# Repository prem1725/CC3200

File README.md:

# CC3200

CC3200 SimpleLink Wi-Fi—Consists of
Applications Microcontroller, Wi-Fi Network
Processor, and Power-Management Subsystems

Wi-Fi CERTIFIED™ Chip

Applications Microcontroller Subsystem
  ARM® Cortex®-M4 Core at 80 MHz
  Embedded Memory
    RAM (Up to 256KB)
    External Serial Flash Bootloader, and Peripheral Drivers in ROM
    
  32-Channel Direct Memory Access (µDMA)

  Hardware Crypto Engine for Advanced Fast Security, Including
    AES, DES, and 3DES
    SHA2 and MD5
    CRC and Checksum

  8-Bit Parallel Camera Interface

  1 Multichannel Audio Serial Port (McASP)
  Interface with Support for Two I2S Channels

  1 SD/MMC Interface

  2 Universal Asynchronous Receivers and
  Transmitters (UARTs)

  1 Serial Peripheral Interface (SPI)

  1 Inter-Integrated Circuit (I2C)

  4 General-Purpose Timers with 16-Bit Pulse-
  Width Modulation (PWM) Mode

  1 Watchdog Timer

  4-Channel 12-Bit Analog-to-Digital Converters
  (ADCs)

  Up to 27 Individually Programmable, Multiplexed
  GPIO Pins

Dedicated External SPI Interface for Serial Flash

Wi-Fi Network Processor Subsystem
  Featuring Wi-Fi Internet-On-a-Chip™
  
  Dedicated ARM MCU
  Completely Offloads Wi-Fi and Internet
  Protocols from the Application Microcontroller
  
  Wi-Fi and Internet Protocols in ROM
  
  802.11 b/g/n Radio, Baseband, Medium Access
  Control (MAC), Wi-Fi Driver, and Supplicant
  
  TCP/IP Stack
    Industry-Standard BSD Socket Application
    Programming Interfaces (APIs)
    
    8 Simultaneous TCP or UDP Sockets
    
    2 Simultaneous TLS and SSL Sockets
  Powerful Crypto Engine for Fast, Secure Wi-Fi
  and Internet Connections with 256-Bit AES
  Encryption for TLS and SSL Connections

  Station, AP, and Wi-Fi Direct™ Modes

  WPA2 Personal and Enterprise Security

  SimpleLink Connection Manager for
  Autonomous and Fast Wi-Fi Connections

  SmartConfig™ Technology, AP Mode, and
  WPS2 for Easy and Flexible Wi-Fi Provisioning

  TX Power
    18.0 dBm @ 1 DSSS
    14.5 dBm @ 54 OFDM

  RX Sensitivity
    –95.7 dBm @ 1 DSSS
    –74.0 dBm @ 54 OFDM

  Application Throughput
    UDP: 16 Mbps
    TCP: 13 Mbps

Power-Management Subsystem
  Integrated DC-DC Supports a Wide Range of
  Supply Voltage:
    VBAT Wide-Voltage Mode: 2.1 to 3.6 V
    
    VIO is Always Tied with VBAT
    
    Preregulated 1.85-V Mode

  Advanced Low-Power Modes
    Hibernate: 4 µA
    
    Low-Power Deep Sleep (LPDS): 250 µA
    
    RX Traffic (MCU Active): 59 mA @ 54 OFDM
    
    TX Traffic (MCU Active): 229 mA @ 54 OFDM,
    Maximum Power

    Idle Connected (MCU in LPDS):
    825 µA @ DTIM = 1

Clock Source
  40.0-MHz Crystal with Internal Oscillator
  
  32.768-kHz Crystal or External RTC Clock

Package and Operating Temperature
  0.5-mm Pitch, 64-Pin, 9-mm × 9-mm QFN
  
  Ambient Temperature Range: –40°C to 85°C

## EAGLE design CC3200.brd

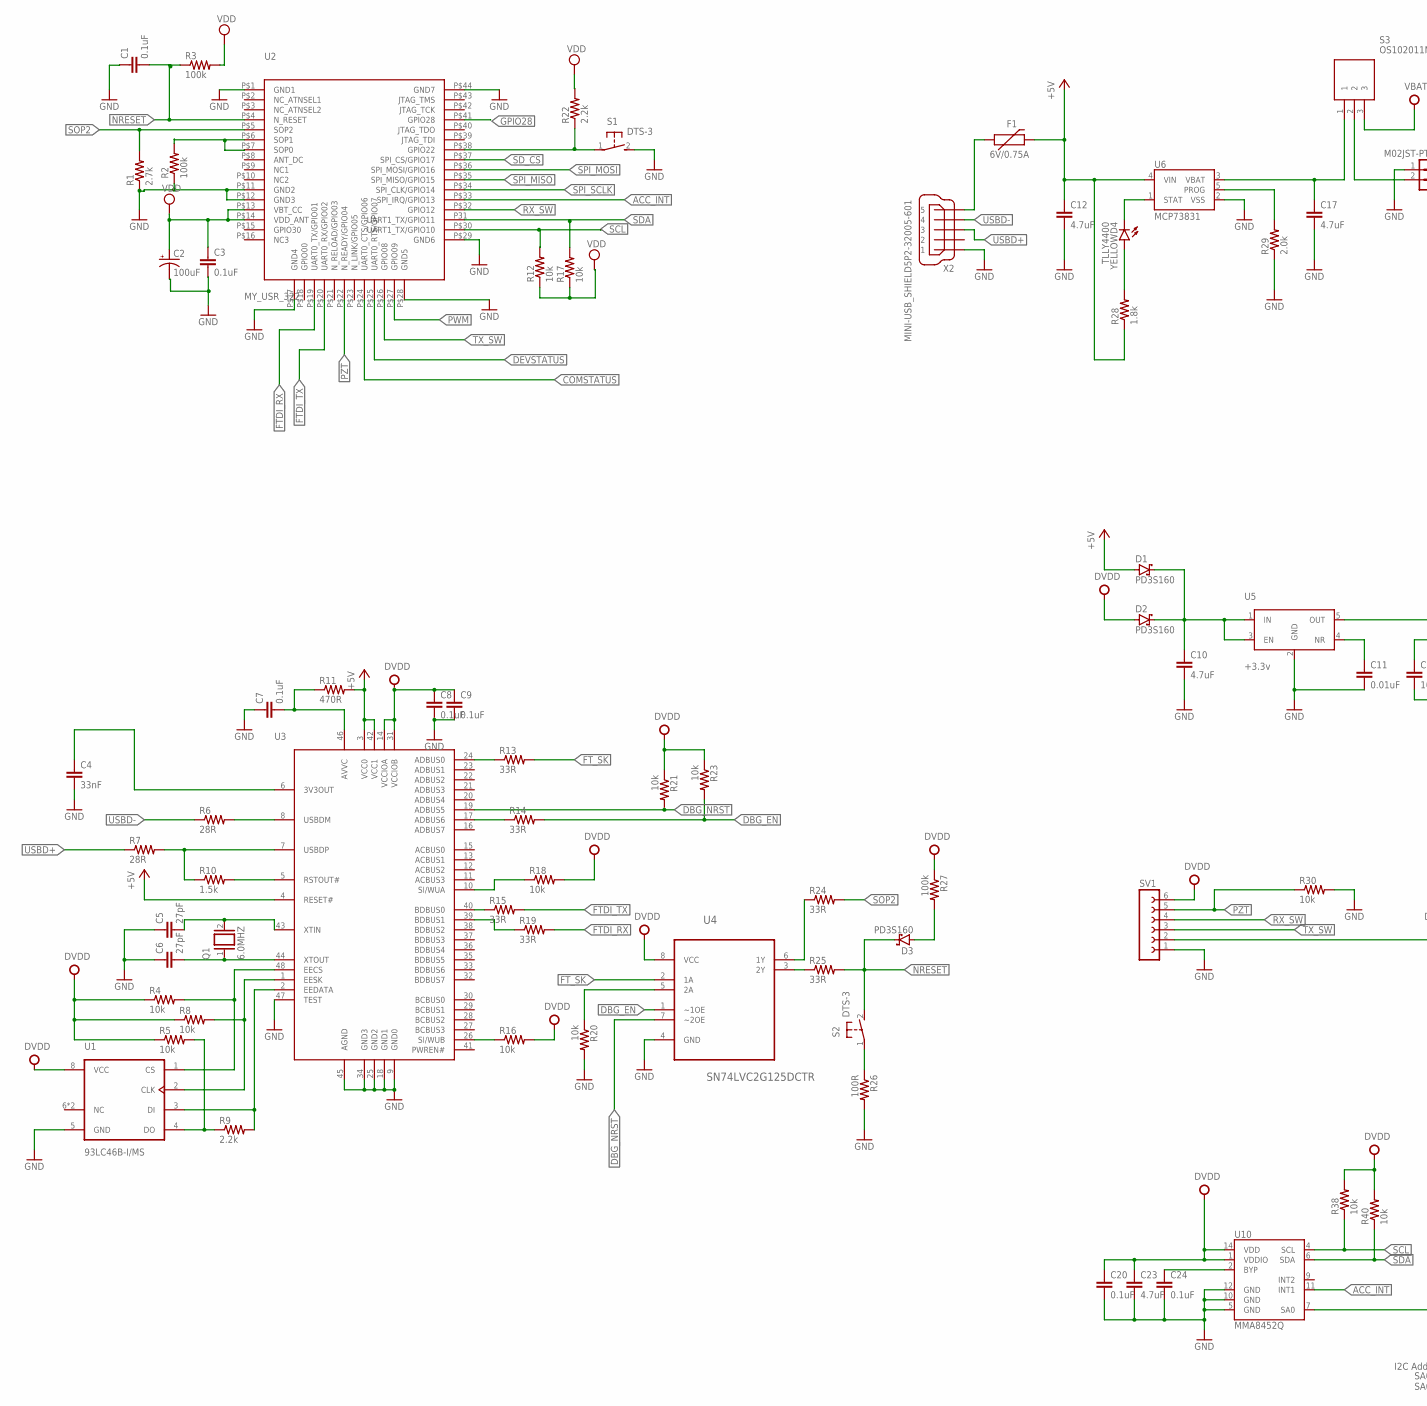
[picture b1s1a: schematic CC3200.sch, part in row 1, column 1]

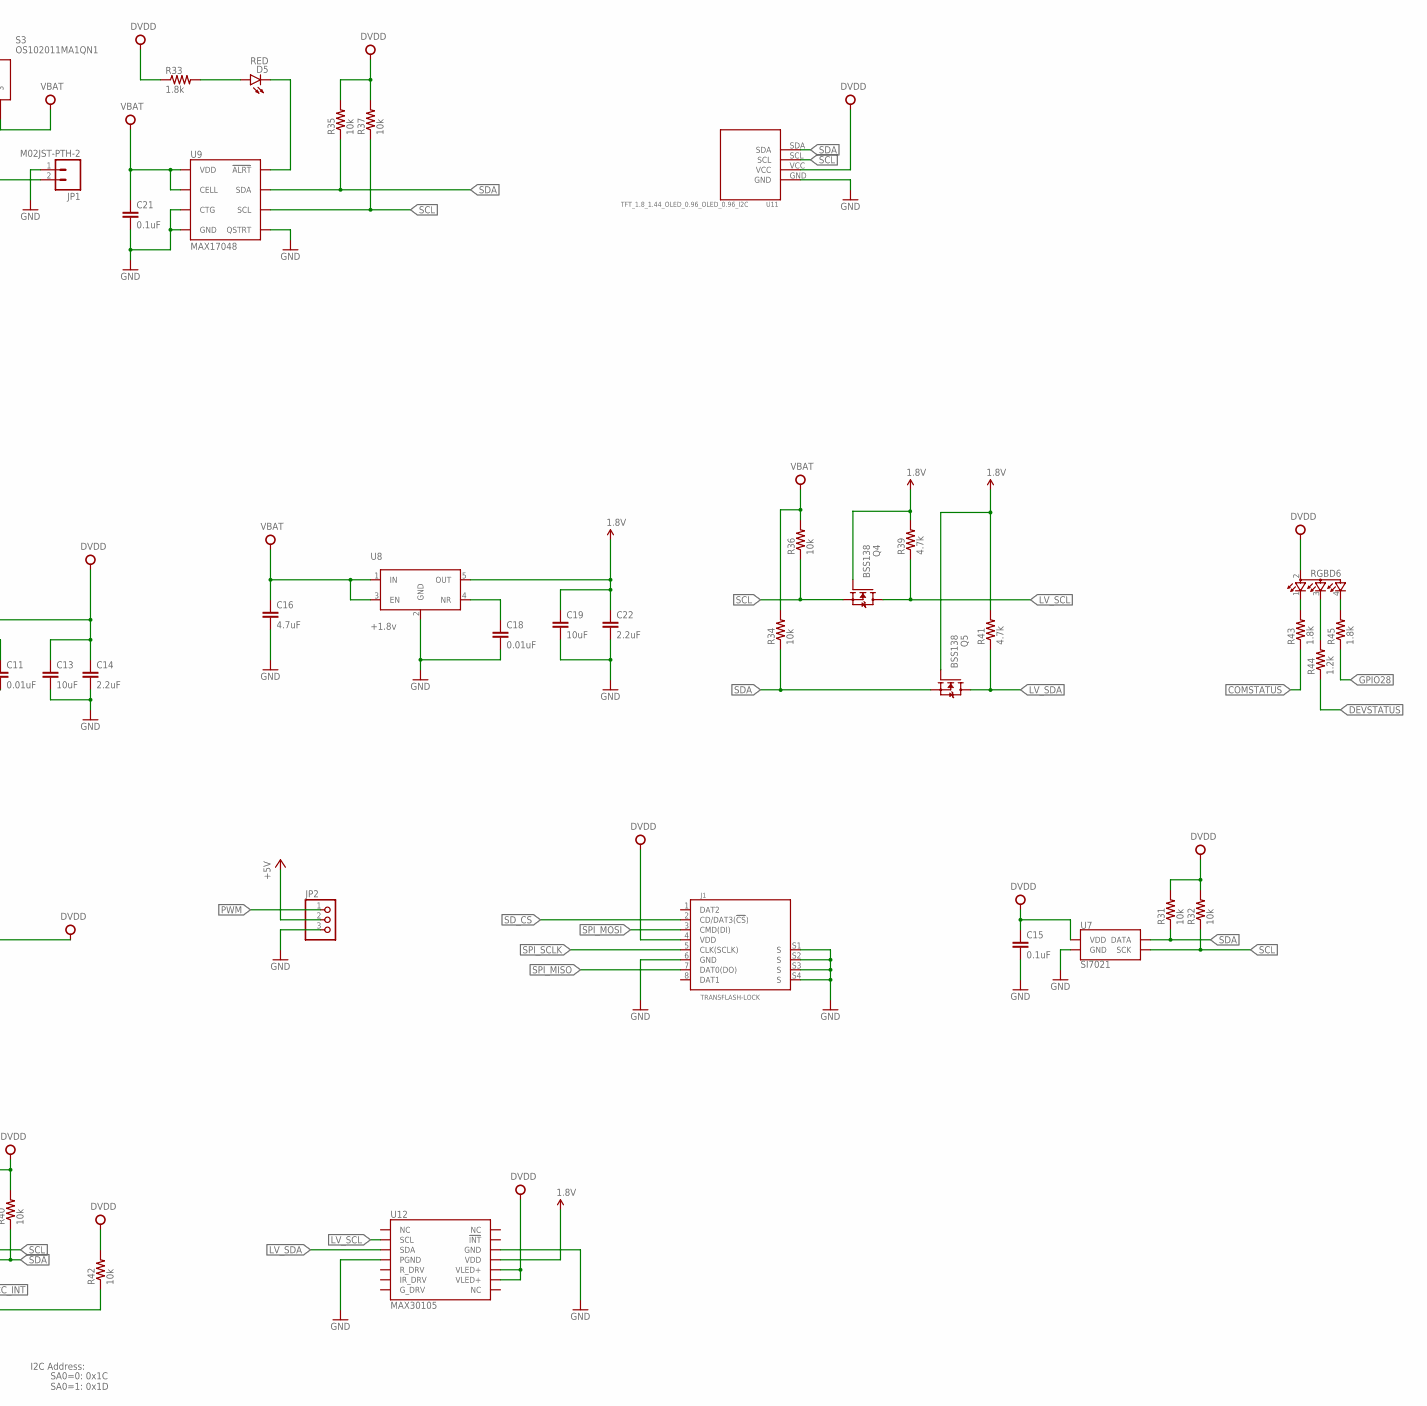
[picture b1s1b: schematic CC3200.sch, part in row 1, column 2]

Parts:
C1, C3: 0.1uF; 0402-TIGHT
C2: 100uF; 1206-POLAR
C4: 33nF; 0603-CAP
C5, C6: 27pF; 0603-CAP
C7, C8, C9, C15, C20, C21, C24: 0.1uF; 0603-CAP
C10, C12, C16, C17, C23: 4.7uF; 0603-CAP
C11, C18: 0.01uF; 0603-CAP
C13, C19: 10uF; 0603-CAP
C14, C22: 2.2uF; 0603-CAP
D1, D2, D3: PD3S160; POWERDI323
D5: RED; LED-0603
F1: 6V/0.75A; 1206
J1: TRANSFLASH-LOCK; TRANSFLASH-LOCK-SOCK
JP1: M02JST-PTH-2; JST-2-PTH
JP2: PINHD-1X3; 1X03
Q1: 6.0MHZ; Q
Q4, Q5: BSS138; SOT23
R1: 2.7k; 0603-RES
R2, R3, R27: 100k; 0603-RES
R4, R5, R8, R12, R16, R17, R18, R20, R21, R23, R30, R31, R32, R34, R35, R36, R37, R38, R40, R42: 10k; 0603-RES
R6, R7: 28R; 0603-RES
R9, R22: 2.2k; 0603-RES
R10: 1.5k; 0603-RES
R11: 470R; 0603-RES
R13, R14, R15, R19, R24, R25: 33R; 0603-RES
R26: 100R; 0603-RES
R28, R33, R43, R45: 1.8k; 0603-RES
R29: 2.0k; 0603-RES
R39, R41: 4.7k; 0603-RES
R44: 1.2k; 0603-RES
RGBD6: TOPLED-3; P-LCC-4-3
S1, S2: DTS-3
S3: OS102011MA1QN1
SV1: FE06-1; FE06
U1: 93LC46B-I/MS; SOP65P490X110-8N
U2: MY_USR_322
U3: FT2232D; LQFP48
U4: SN74LVC2G125DCTR; SOP65P400X130-8N
U5: +3.3v; SOT23-5
U6: MCP73831; SOT23-5
U7: SI7021; DFN-6-3X3-SI7021
U8: +1.8v; SOT23-5
U9: MAX17048; DFN-8
U10: MMA8452Q; QFN-16_0.5MM
U11: TFT_1.8_1.44_OLED_0.96_OLED_0.96_I2C
U12: MAX30105; OLGA-14
X2: MINI-USB_SHIELD5P2-32005-601; 32005-601
YELLOWD4: TLLY4400; LED3MM

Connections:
1.8V: C19.1, C22.1, Q5.1 (G), R39.2, R41.2, U8.5 (OUT), U12.11 (VDD)
+5V: C12.1, D1.A, F1.2, JP2.2, R11.2, R28.1, U3.3 (VCC0), U3.4 (RESET#), U3.42 (VCC1), U6.4 (VIN)
ACC_INT: U2.P$33 (SPI_IRQ/GPIO13), U10.11 (INT1)
COMSTATUS: R43.1, U2.P$24 (UART0_CTS/GPIO06)
DBG_EN: R14.2, R23.2, U4.1 (~1OE)
DBG_NRST: R21.2, U3.19 (ADBUS5), U4.7 (~2OE)
DEVSTATUS: R44.1, U2.P$25 (UART0_RTS/GPIO07)
DVDD: C8.1, C9.1, C13.1, C14.1, C15.1, C20.1, C23.1, D2.A, J1.4 (VDD), R4.1, R5.1, R8.1, R16.2, R18.2, R21.1, R23.1, R27.1, R31.2, R32.2, R33.1, R35.2, R37.2, R38.2, R40.2, R42.2, RGBD6.2 (A2), SV1.2, SV1.6, U1.8 (VCC), U3.14 (VCCIOA), U3.31 (VCCIOB), U4.8 (VCC), U5.5 (OUT), U7.VDD, U10.1 (VDDIO), U10.14 (VDD), U11.VCC, U12.9 (VLED+), U12.10 (VLED+)
FTDI_RX: R19.2, U2.P$19 (UART0_TX/GPIO01)
FTDI_TX: R15.2, U2.P$20 (UART0_RX/GPIO02)
FT_SK: R13.2, U4.2 (1A)
GND: C1.1, C3.2, C4.2, C5.1, C6.1, C7.1, C8.2, C9.2, C10.2, C11.2, C12.2, C13.2, C14.2, C15.2, C16.2, C17.2, C18.2, C19.2, C20.2, C21.2, C22.2, C23.2, C24.2, J1.6 (GND), J1.S1 (S), J1.S2 (S), J1.S3 (S), J1.S4 (S), JP1.1, JP2.3, R1.1, R20.2, R26.2, R29.1, R30.2, S1.2, SV1.1, U1.5 (GND), U2.P$1 (GND1), U2.P$11 (GND2), U2.P$17 (GND4), U2.P$28 (GND5), U2.P$29 (GND6), U2.P$44 (GND7), U3.9 (GND0), U3.18 (GND1), U3.25 (GND2), U3.34 (GND3), U3.45 (AGND), U3.47 (TEST), U4.4 (GND), U5.2 (GND), U6.2 (VSS), U7.GND, U8.2 (GND), U9.P$1 (CTG), U9.P$4 (GND), U9.P$6 (QSTRT), U9.P$9 (GND), U10.5 (GND), U10.10 (GND), U10.12 (GND), U11.GND, U12.4 (PGND), U12.12 (GND), X2.1
GPIO28: R45.1, U2.P$41 (GPIO28)
LV_SCL: R39.1, U12.2 (SCL)
LV_SDA: Q5.3 (D), R41.1, U12.3 (SDA)
unnamed: S1.1, U2.P$38 (GPIO22)
unnamed: R2.2, U2.P$6 (SOP1)
unnamed: C4.1, U3.6 (3V3OUT)
unnamed: R6.2, U3.8 (USBDM)
unnamed: R7.2, R10.1, U3.7 (USBDP)
unnamed: R10.2, U3.5 (RSTOUT#)
unnamed: C5.2, Q1.2, U3.43 (XTIN)
unnamed: C6.2, Q1.1, U3.44 (XTOUT)
unnamed: R9.2, U1.3 (DI), U3.2 (EEDATA)
unnamed: R5.2, R9.1, U1.4 (DO)
unnamed: R8.2, U1.2 (CLK), U3.1 (EESK)
unnamed: R4.2, U1.1 (CS), U3.48 (EECS)
unnamed: C7.2, R11.1, U3.46 (AVVC)
unnamed: R13.1, U3.24 (ADBUS0)
unnamed: R14.1, U3.17 (ADBUS6)
unnamed: R18.1, U3.10 (SI/WUA)
unnamed: R15.1, U3.40 (BDBUS0)
unnamed: R19.1, U3.39 (BDBUS1)
unnamed: R16.1, U3.26 (SI/WUB)
unnamed: R20.1, U4.5 (2A)
unnamed: R25.1, U4.3 (2Y)
unnamed: D3.A, R27.2
unnamed: R24.1, U4.6 (1Y)
unnamed: R26.1, S2.1
unnamed: D5.C, U9.P$5 (!ALRT)
unnamed: D5.A, R33.2
unnamed: JP1.2, S3.2
unnamed: R29.2, U6.5 (PROG)
unnamed: C17.1, S3.1, U6.3 (VBAT)
unnamed: U6.1 (STAT), YELLOWD4.K (C)
unnamed: R28.2, YELLOWD4.A
unnamed: F1.1, X2.5
unnamed: C10.1, D1.C, D2.C, U5.1 (IN), U5.3 (EN)
unnamed: C11.1, U5.4 (NR)
unnamed: C18.1, U8.4 (NR)
unnamed: R43.2, RGBD6.1 (CRED)
unnamed: R44.2, RGBD6.3 (CBLUE)
unnamed: R45.2, RGBD6.4 (CGREEN)
unnamed: C24.1, U10.2 (BYP)
unnamed: R42.1, U10.7 (SA0)
NRESET: D3.C, R25.2, S2.2, U2.P$4 (N_RESET)
PWM: JP2.1, U2.P$27 (GPIO09)
PZT: R30.1, SV1.5, U2.P$22 (N_READY/GPIO04)
RX_SW: SV1.4, U2.P$32 (GPIO12)
SCL: R32.1, R36.1, R37.1, R38.1, U2.P$30 (UART1_TX/GPIO10), U7.SCK, U9.P$7 (SCL), U10.4 (SCL), U11.SCL
SDA: R31.1, R34.1, R35.1, R40.1, U2.P31 (UART1_TX/GPIO11), U7.DATA, U9.P$8 (SDA), U10.6 (SDA), U11.SDA
SD_CS: J1.2 (CD/DAT3(!CS!)), U2.P$37 (SPI_CS/GPIO17)
SOP2: R1.2, R24.2, U2.P$5 (SOP2)
SPI_MISO: J1.7 (DAT0(DO)), U2.P$35 (SPI_MISO/GPIO15)
SPI_MOSI: J1.3 (CMD(DI)), U2.P$36 (SPI_MOSI/GPIO16)
SPI_SCLK: J1.5 (CLK(SCLK)), U2.P$34 (SPI_CLK/GPIO14)
TX_SW: SV1.3, U2.P$26 (GPIO08)
USBD+: R7.1, X2.3
USBD-: R6.1, X2.4
VBAT: C16.1, C21.1, R34.2, R36.2, S3.3, U8.1 (IN), U8.3 (EN), U9.P$2 (CELL), U9.P$3 (VDD)
VDD: C2.1 (+), R3.2, R12.1, R17.1, R22.2, U2.P$14 (VDD_ANT)

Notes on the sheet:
I2C Address:
SA0=0: 0x1C SA0=1: 0x1D

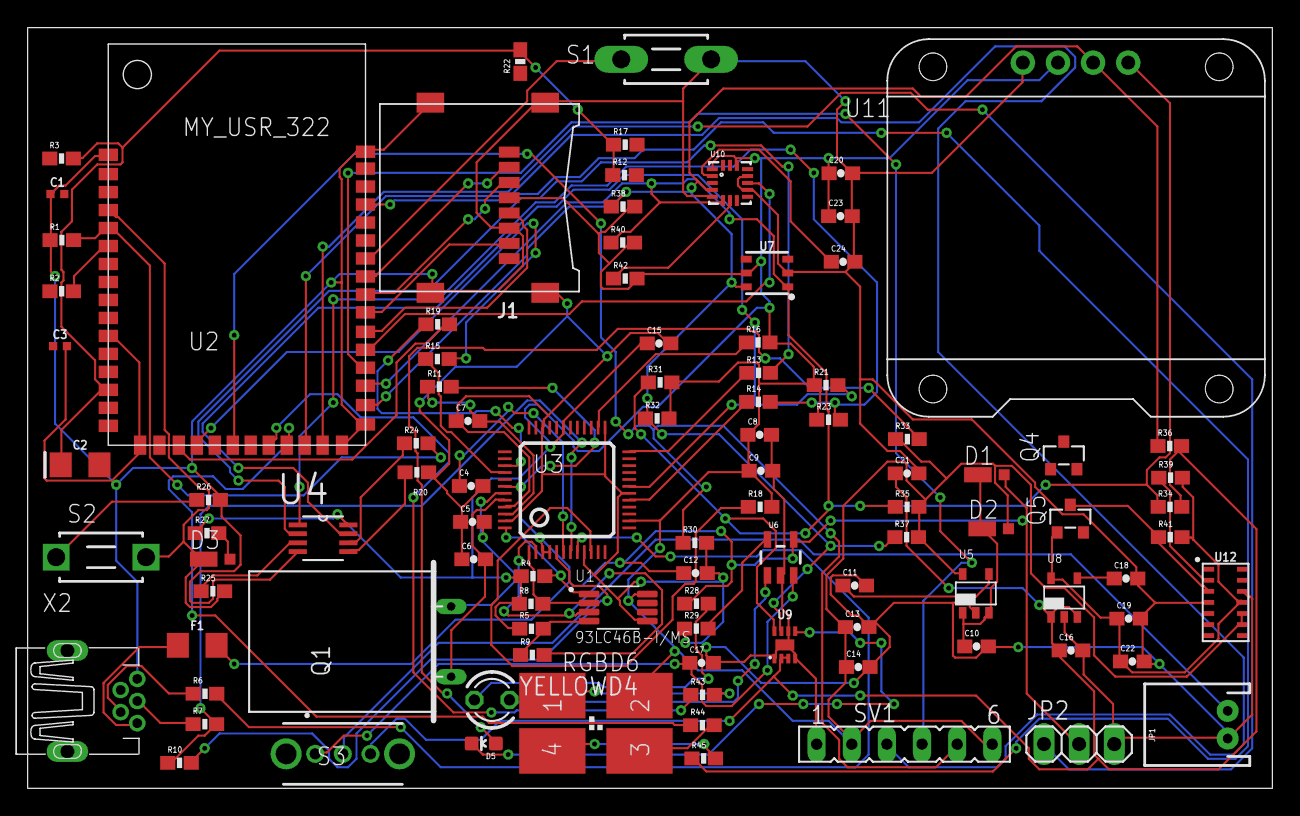
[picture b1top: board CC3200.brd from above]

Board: 2 copper layers, 90.0 x 55.0 mm, 99 parts (0 on the bottom side), 71 nets.

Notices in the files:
parts and their libraries:
SparkFun-Capacitors: Licensing: Creative Commons ShareAlike 4.0 International - https://creativecommons.org/licenses/by-sa/4.0
